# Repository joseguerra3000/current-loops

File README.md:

Lazos de Corriente
==================

Diseno de Modulo de lazos de corriente para monitoreo de sensores tipo ON-OFF a largas distancias.

Montado y probado, obteniendo excelentes resultados con sistemas basados Arduino (+5v) y PIC (+3.3v).

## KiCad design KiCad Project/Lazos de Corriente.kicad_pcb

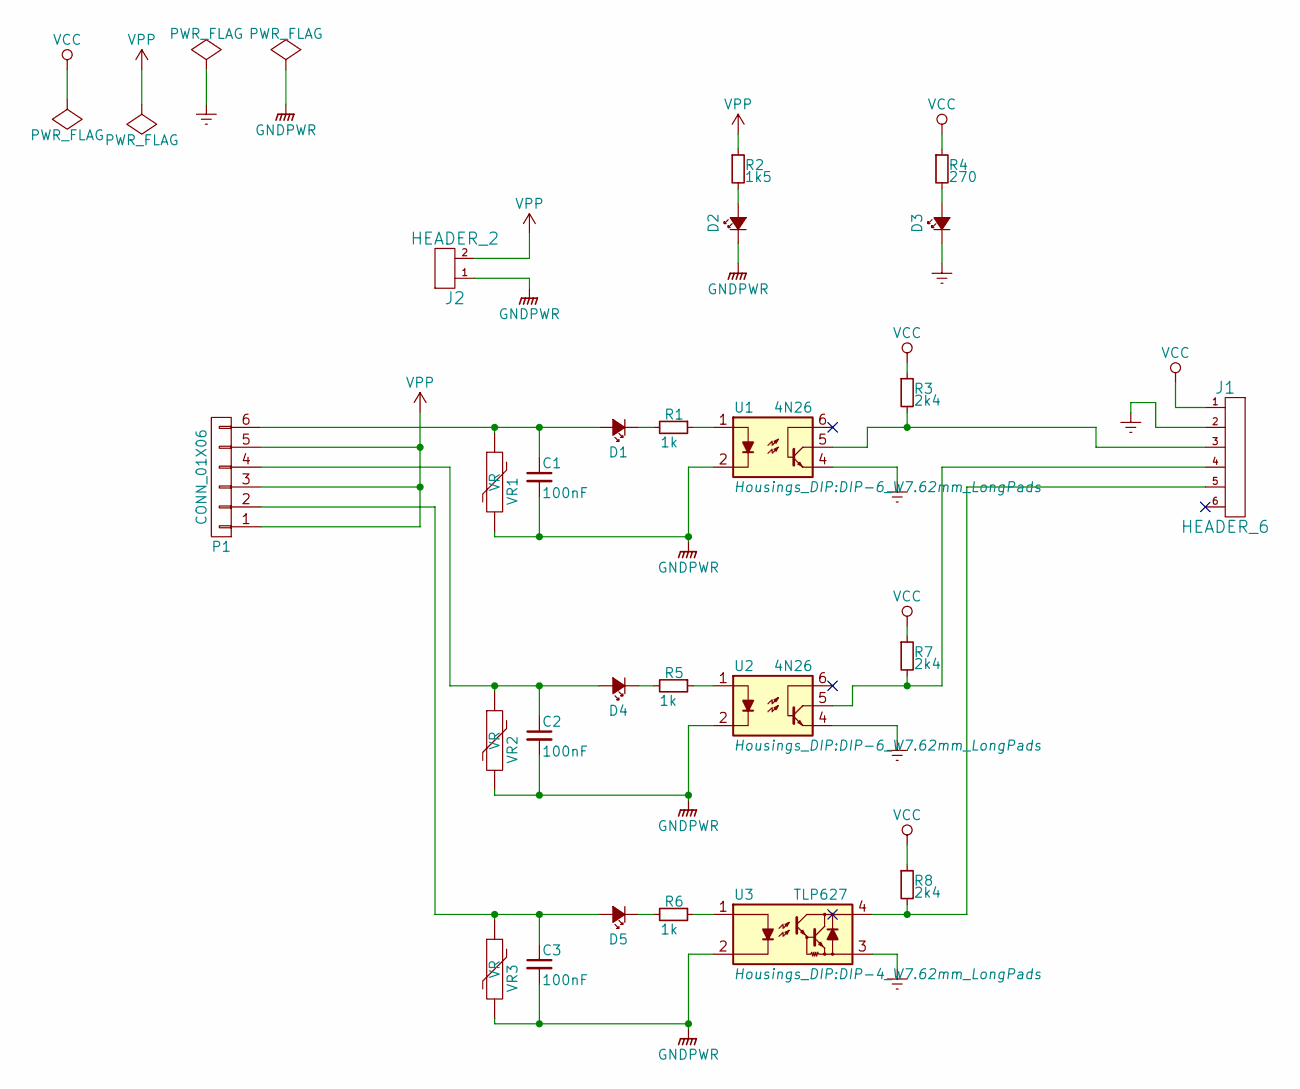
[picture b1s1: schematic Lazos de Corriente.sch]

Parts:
C1, C2, C3: 100nF; cnp_13x4mm
D1, D4, D5: Led_Small; LED-3MM
D2, D3: Led_Small; LED-5MM
J1: HEADER_6; Pin_Header_Angled_1x06
J2: HEADER_2; Pin_Header_Straight_1x02
P1: CONN_01X06; TerminalBlock_Pheonix_MPT-2.54mm_6pol
R1, R5, R6: 1k; RC07
R2: 1k5; RC07
R3, R7, R8: 2k4; RC07
R4: 270; RC07
U1, U2: 4N26; DIP-6_W7.62mm_LongPads
U3: TLP627; DIP-4_W7.62mm_LongPads
VR1, VR2, VR3: VR; RV_Disc_D7_W3.5_P5

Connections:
Earth: D3.1 (K), J1.2, U1.4, U2.4, U3.3
GNDPWR: C1.2, C2.2, C3.2, D2.1 (K), J2.1, U1.2, U2.2, U3.2, VR1.2, VR2.2, VR3.2
unnamed: C1.1, D1.2 (A), P1.6, VR1.1
unnamed: C2.1, D4.2 (A), P1.4, VR2.1
unnamed: C3.1, D5.2 (A), P1.2, VR3.1
unnamed: D1.1 (K), R1.2
unnamed: D2.2 (A), R2.2
unnamed: D3.2 (A), R4.2
unnamed: D4.1 (K), R5.2
unnamed: D5.1 (K), R6.2
unnamed: J1.3, R3.2, U1.5
unnamed: J1.4, R7.2, U2.5
unnamed: J1.5, R8.2, U3.4
unnamed: R1.1, U1.1
unnamed: R5.1, U2.1
unnamed: R6.1, U3.1
VCC: J1.1, R3.1, R4.1, R7.1, R8.1
VPP: J2.2, P1.1, P1.3, P1.5, R2.1

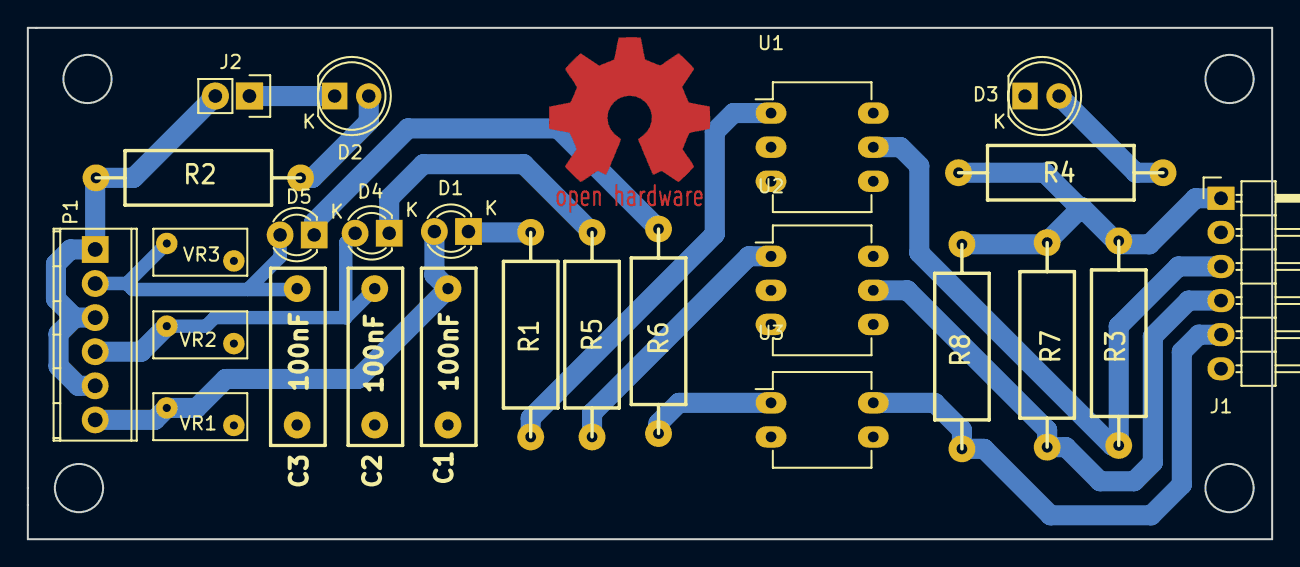
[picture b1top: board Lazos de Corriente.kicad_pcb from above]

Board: 2 copper layers, 92.7 x 38.1 mm, 25 parts (0 on the bottom side), 18 nets.
